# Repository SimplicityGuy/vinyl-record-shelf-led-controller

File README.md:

# WS2812B LED Controller — Vinyl Record Shelf Finder

PCB for the hardware layer of the vinyl record shelf finder: a system that illuminates the correct cube of a Kallax 4×4 shelf when you look up a vinyl record. The shelf-finder application lives in [vinyl-record-shelf-gopher](https://github.com/SimplicityGuy/vinyl-record-shelf-gopher) and uses record metadata from [discogsography](https://github.com/SimplicityGuy/discogsography).

## Overview

A Raspberry Pi 4B queries a PostgreSQL database for a record's shelf location, then fires an HTTP call to WLED running on a Seeed XIAO ESP32C6. The ESP32C6 drives the correct WS2812B LED strip, lighting up the cube containing that record.

```mermaid
flowchart TD
    PI[Raspberry Pi 4B]
    ESP["XIAO ESP32C6<br/>(WLED)"]
    LS["74AHCT125<br/>3.3V → 5V level shift"]
    C1[Cube 1 LEDs]
    C2[Cube 2 LEDs]
    C16[Cube 16 LEDs]

    PI -->|WiFi HTTP| ESP
    ESP --> LS
    LS --> C1
    LS --> C2
    LS -.-> C16
```

## PCB Specifications

| Parameter | Value |
|---|---|
| Dimensions | 68 × 50 mm |
| Layers | 2 (F.Cu, B.Cu) |
| Min trace width | 0.25 mm (signal) / 1.0 mm (power) |
| PCB thickness | 1.6 mm |
| Surface finish | ENIG (OSH Park) |
| Assembly | All through-hole, hand solderable |
| Mounting | 4 × M3 corner holes, 10 mm standoffs |
| Connectors | Top edge: USB-C (XIAO), DC barrel jack, LED terminal block |

## Schematic

The signal path:

```mermaid
flowchart TD
    A["XIAO D1<br/>GPIO3 (3.3V)"]
    B[R1 470Ω series]
    C["U2 74AHCT125<br/>1A → 1Y<br/>3.3V → 5V shift"]
    D[J2 DATA pin]
    E[WS2812B Strip Din]

    A --> B --> C --> D --> E
```

Power:
- 5V in via J1 (CUI PJ-102AH barrel jack, center positive)
- 5V rail shared between LED strips (via J2) and XIAO VBUS
- 3.3V generated by XIAO's onboard regulator → decoupled by C4

## Bill of Materials

See [BOM.csv](docs/BOM.csv) for the full sourced BOM with DigiKey part numbers.

| Ref | Part | Description | Qty |
|---|---|---|---|
| U1 | XIAO-ESP32-C6 | Seeed XIAO ESP32C6 module | 1 |
| U2 | SN74AHCT125N | 74AHCT125 level shifter, DIP-14 | 1 |
| — | ED14DT | On Shore DIP-14 socket | 1 |
| C1 | UKL1C101KPDANA | Nichicon 100µF/16V electrolytic, P3.5mm | 1 |
| C2, C3, C4 | K104K15X7RF53H5G | Vishay KG 100nF X7R, 50V, P5.0mm | 3 |
| R1 | LR1F470R | TE 470Ω ¼W axial, P7.62mm | 1 |
| J1 | PJ-102AH | CUI DC barrel jack 2.1mm right-angle | 1 |
| J2 | 0397000803 | Molex 3-pos Eurostyle terminal block 5.00mm | 1 |
| MH1–4 | — | M3 × 6mm screws + 10mm brass standoffs | 4 |

## LED Strip Wiring

16 × WS2812B strips (one per Kallax cube). All strips share the 5V/GND power bus. Data is a single daisy-chain through all 16.

```
J2 +5V ──────────────────────── ●  ●  ●  ... ●   (all 16 strip +5V pads)
J2 GND ──────────────────────── ●  ●  ●  ... ●   (all 16 strip GND pads)
J2 DATA → Strip1 Din
           Strip1 Dout → Strip2 Din
                          Strip2 Dout → ... → Strip16 Din
```

Cube numbering (top-left = 1, bottom-right = 16, row-major):

```
┌────┬────┬────┬────┐
│  1 │  2 │  3 │  4 │  ← Row 1
├────┼────┼────┼────┤
│  5 │  6 │  7 │  8 │  ← Row 2
├────┼────┼────┼────┤
│  9 │ 10 │ 11 │ 12 │  ← Row 3
├────┼────┼────┼────┤
│ 13 │ 14 │ 15 │ 16 │  ← Row 4
└────┴────┴────┴────┘
```

## WLED Configuration

| Setting | Value |
|---|---|
| LED type | WS2812B |
| Data pin | GPIO3 (D1) |
| Total LEDs | 16 × (LEDs per strip) |
| Segments | 16 (one per cube, equal length) |
| Color order | GRB |
| Voltage | 5V |

Each cube maps to one WLED segment. The [vinyl-record-shelf-gopher](https://github.com/SimplicityGuy/vinyl-record-shelf-gopher) service sends an HTTP request to activate the segment corresponding to the record's cube location. API specification: TBD.

## J1 Barrel Jack Pinout

| Pin | Function | Note |
|---|---|---|
| 1 (sleeve, square pad) | GND | |
| 2 (tip) | +5V | Center positive |
| 3 (switch, side) | GND | Tied to GND on PCB |

⚠️ **Center positive only.** Verify polarity with a multimeter before first power-up.

## J2 Terminal Block Pinout

| Pin | Signal | Wire color |
|---|---|---|
| 1 (square pad) | +5V | Red |
| 2 | GND | Black |
| 3 | DATA (5V logic) | Yellow |

## Assembly

See [ASSEMBLY.md](docs/ASSEMBLY.md) for the full step-by-step guide covering PCB population, LED strip installation, wiring, and system test.

**Soldering order (shortest to tallest):**
1. R1 (470Ω axial)
2. C2, C3, C4 (100nF ceramic disc)
3. C1 (100µF electrolytic — observe polarity)
4. ED14DT DIP socket (not the IC)
5. J1 barrel jack
6. J2 terminal block
7. XIAO female socket headers (1×7 × 2)
8. SN74AHCT125N into socket (after power test)
9. XIAO ESP32C6 module

## Fabrication

Designed for [OSH Park](https://oshpark.com) 2-layer service. Upload `controller/ws2812b_controller.kicad_pcb` directly.

To generate gerbers in KiCAD 7:
1. Open `controller/ws2812b_controller.kicad_pcb`
2. File → Fabrication Outputs → Gerbers
3. Output to `controller/gerbers/`
4. Also generate drill files from the same dialog

## Software

WLED firmware is flashed to the XIAO ESP32C6 before installation. The shelf-finder application lives in [vinyl-record-shelf-gopher](https://github.com/SimplicityGuy/vinyl-record-shelf-gopher), which consumes record metadata from [discogsography](https://github.com/SimplicityGuy/discogsography) and issues the WLED segment calls to this controller. API specification: TBD.

## License

Hardware designs released under [CERN OHL-P v2](LICENSE).

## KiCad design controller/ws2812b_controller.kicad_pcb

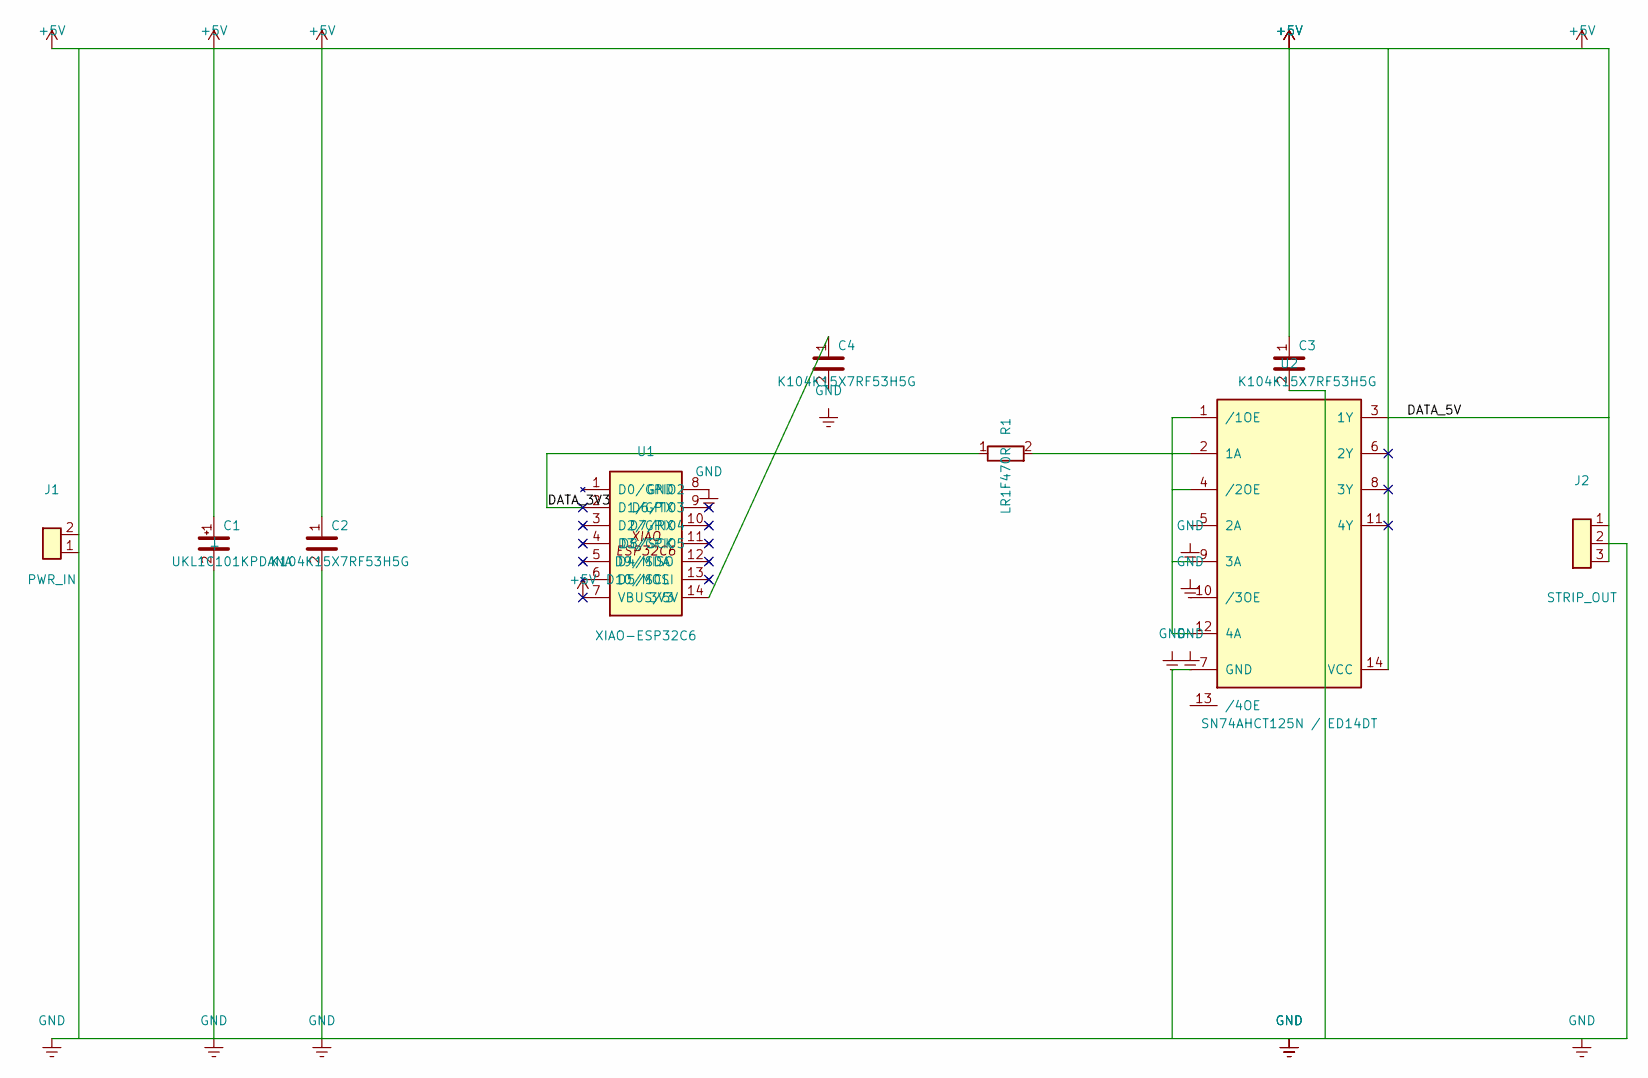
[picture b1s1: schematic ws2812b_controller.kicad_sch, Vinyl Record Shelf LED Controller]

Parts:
C1: UKL1C101KPDANA; CP_Radial_D8.0mm_P3.50mm
C2, C3, C4: K104K15X7RF53H5G; C_Disc_D3.4mm_W2.1mm_P5.00mm
J1: PWR_IN; BarrelJack_CUI_PJ-102AH_Horizontal
J2: STRIP_OUT; TerminalBlock_Phoenix_MKDS-1,5-3_1x03_P5.00mm_Horizontal
R1: LR1F470R; R_Axial_DIN0207_L6.3mm_D2.5mm_P7.62mm
U1: XIAO-ESP32C6; XIAO-ESP32-C6-DIP
U2: SN74AHCT125N / ED14DT; DIP-14_W7.62mm

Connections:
+5V: C1.1 (+), C2.1, C3.1, J2.3, U1.7 (VBUS/5V)
/DATA_3V3: R1.1, U1.2 (D1/GPIO3)
/DATA_5V: U2.3 (1Y)
GND: C1.2 (-), C2.2, J2.2, U1.8 (GND)
unnamed: C4.1, U1.14 (3V3)
unnamed: R1.2, U2.2 (1A)
unnamed: U2.1 (/1OE), U2.12 (4A)

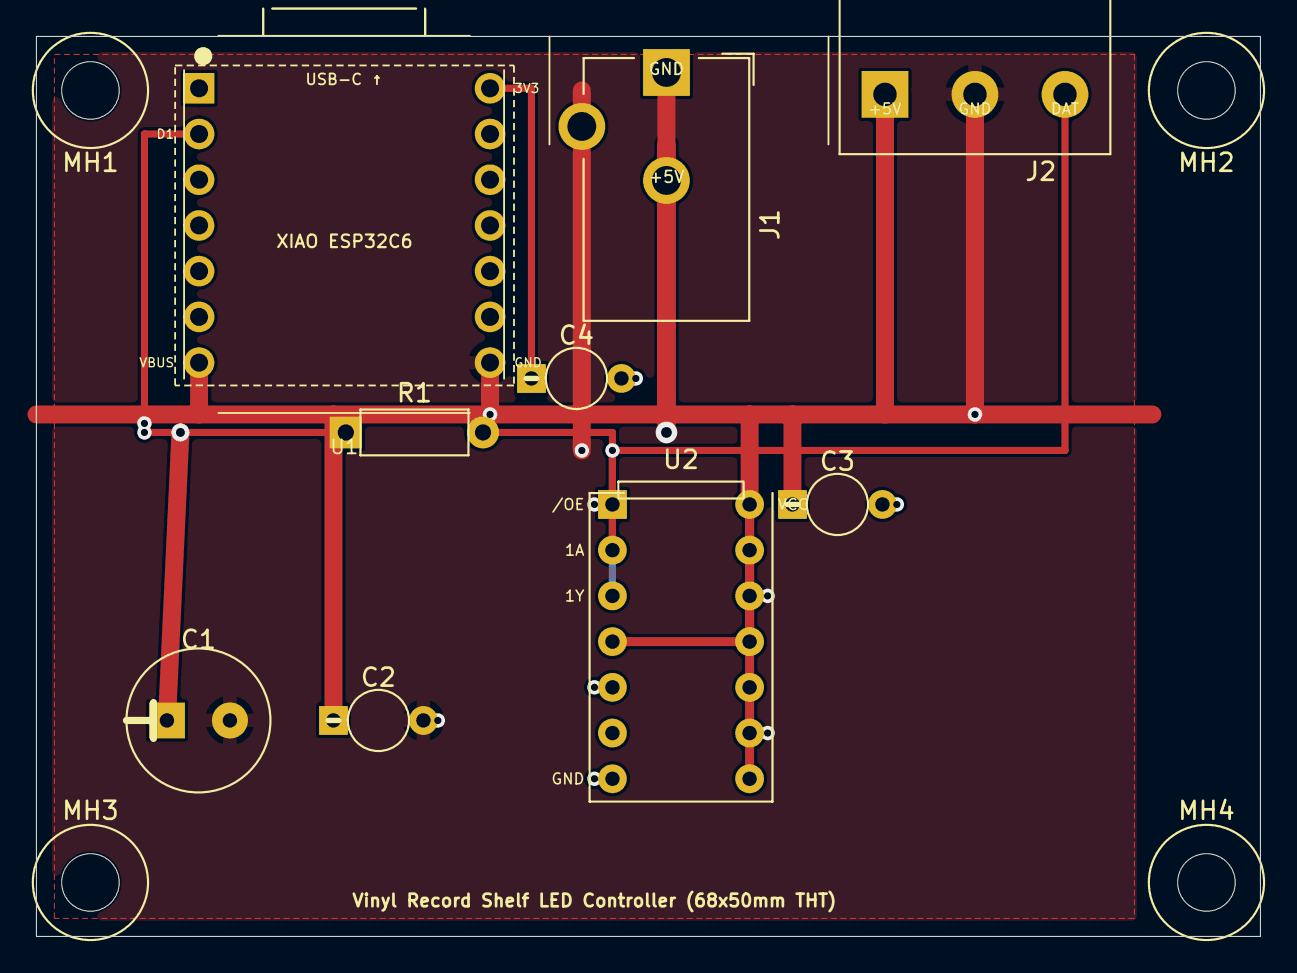
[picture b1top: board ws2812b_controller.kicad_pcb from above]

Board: 2 copper layers, 68.0 x 50.0 mm, 13 parts (0 on the bottom side), 6 nets.

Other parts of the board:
MH1, MH2, MH3, MH4: M3; MountingHole_3.2mm_M3

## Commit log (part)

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2026-04-16 chore: cleanup
